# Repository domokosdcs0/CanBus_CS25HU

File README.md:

# CanBus_CS25HU
PCB for the CanBus team's CanSat for CanSat Hungary 2025.

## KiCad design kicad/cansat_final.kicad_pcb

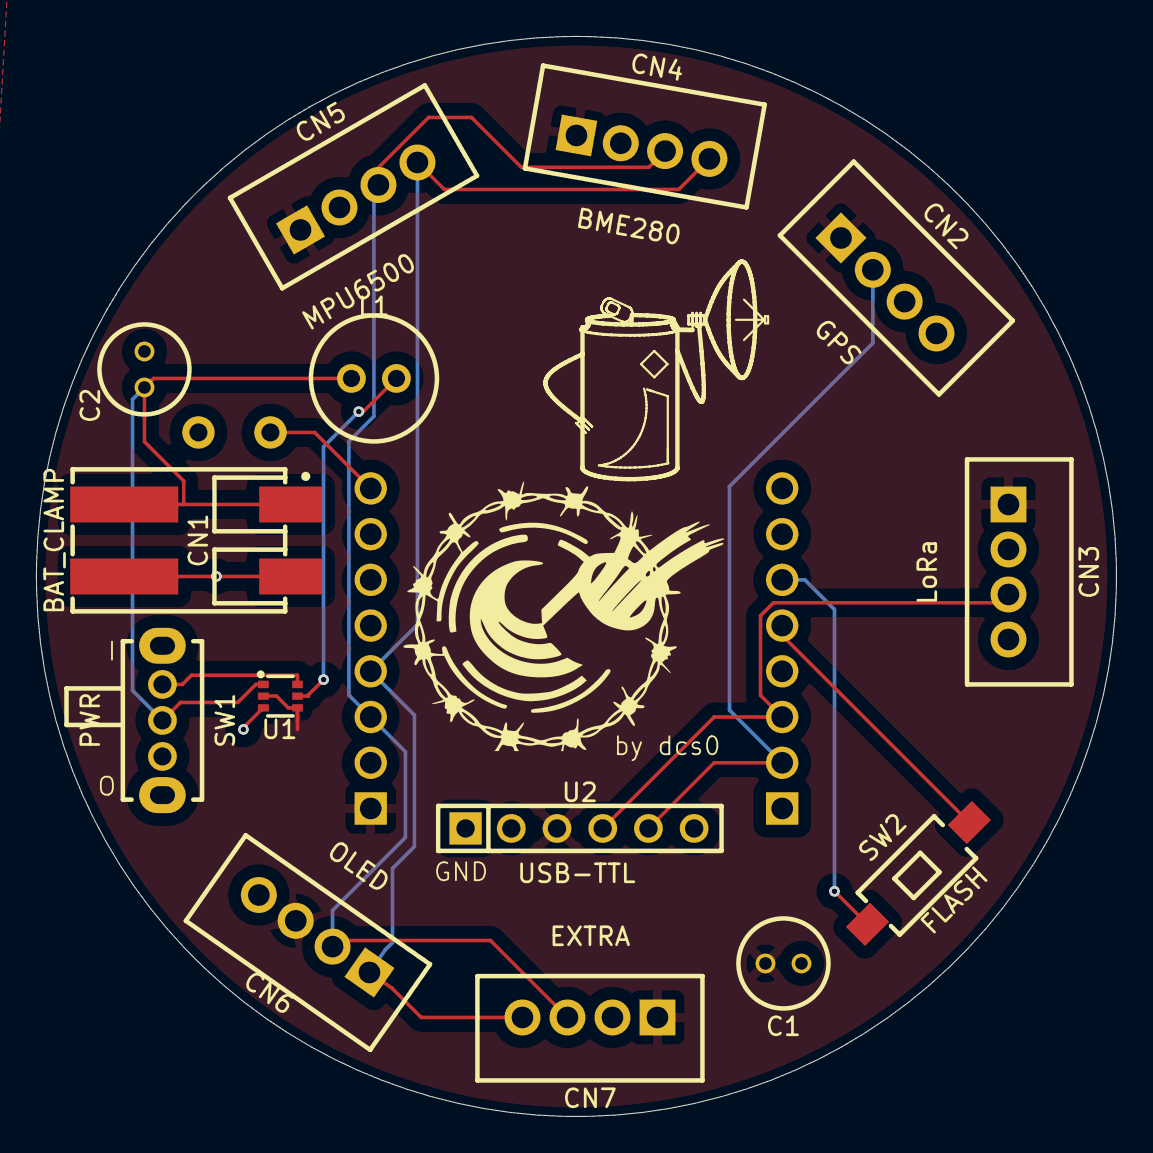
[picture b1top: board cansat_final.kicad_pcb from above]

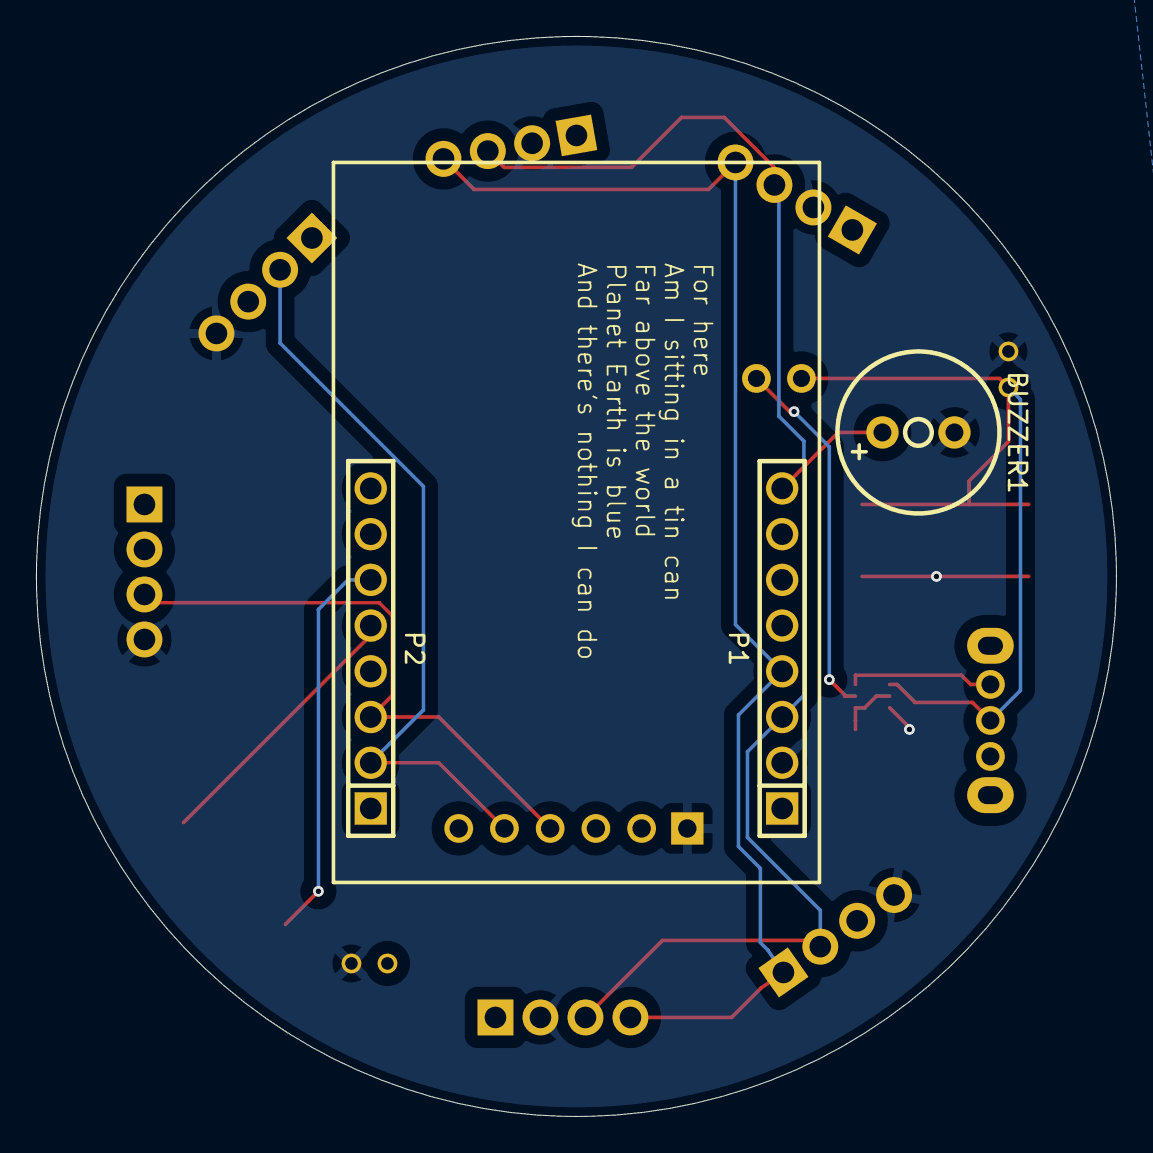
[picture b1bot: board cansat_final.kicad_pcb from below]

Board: 2 copper layers, 60.0 x 60.0 mm, 17 parts (3 on the bottom side), 12 nets.

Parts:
BUZZER1: QMB-09B-03; BUZ-TH_BD9.0-P4.00-D0.6-FD
C1, C2: 10uF; CAP-TH_BD5.0-P2.00-D0.5-FD-1
CN1: BAT_CLAMP; CONN-SMD_2P-P4.00_HDGC4001SMD-S-2P
CN2: GPS; CONN-TH_XH-4A
CN3: LoRa; CONN-TH_XH-4A
CN4: BME280; CONN-TH_XH-4A
CN5: MPU6500; CONN-TH_XH-4A
CN6: OLED; CONN-TH_XH-4A
CN7: EXTRA; CONN-TH_XH-4A
L1: PK0608-100MB; IND-TH_BD7.0-P2.50-D0.7
P1: ESP_L; HDR-TH_8P-P2.54-V-F-1
P2: ESP_R; HDR-TH_8P-P2.54-V-F-1
SW1: PWR; SW-TH_SK12D07VG3
SW2: FLASH; SW-SMD_L6.0-W3.3-LS8.0
U1: TPS61222; SC-70-6_L2.2-W1.3-P0.65-LS2.1-BR
U2: USB-TTL; HDR-TH_6P-P2.54-V-F

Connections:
+5V: C1.1, CN2.1, CN3.1, CN4.1, CN5.1, CN6.3, CN7.1, P1.1, U1.2 (FB), U1.4 (VOUT), U2.3
+BATT: C2.1, CN1.1, L1.1, SW1.2, U1.1 (VIN)
GND: BUZZER1.2, C1.2, C2.2, CN1.2, CN2.4, CN3.4, CN4.2, CN5.2, CN6.4, CN7.2, P1.2, U1.3 (GND), U2.1
unnamed: BUZZER1.1, P1.8
unnamed: P2.5, SW2.2
unnamed: P2.6, SW2.1
unnamed: SW1.1, U1.6 (EN)
unnamed: L1.2, U1.5 (L)
RX: CN3.3, P2.3, U2.4
SCL: CN4.3, CN5.3, CN6.2, CN7.3, P1.3
SDA: CN4.4, CN5.4, CN6.1, CN7.4, P1.4
TX: CN2.2, P2.2, U2.5

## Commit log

2025-01-31 Create LICENSE
2025-01-31 upload board files
